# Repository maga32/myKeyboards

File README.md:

[<< 키보드 종류 보기](../../)

---

# GripKey

<br>

조이콘처럼 한손/양손에 쥐고 사용하는 마우스 겸 키보드 

## 1. 특징

### 1.1. 한손에 쥐고 사용가능한 가벼움과 편리성

- 한손에 쥐고 사용 가능한 크기와 무게로 제작되어 손목에 부담이 없습니다.
- 각각 1000mAh 배터리를 탑재하여 장시간 사용 가능합니다.
- 따로 키보드 위치를 고정해놓을 필요가 없어, 편한 자세로 누워서 사용하기에도 좋습니다.
- !! 한쪽 기기만 사용하여 휴대폰, 태블릿으로 웹툰/소설/쇼츠 감상용으로 사용하기에도 매우 유용합니다. !!
<br>
<br>

### 1.2. 부족함없는 키 개수와 기능
<br>

- 한쪽당 (5x3 +3) 18키로, 양쪽 모두 사용시 36키가 되어 일반적인 키보드의 기능을 모두 활용할 수 있습니다.
- 추가로 5방향(상,하,좌,우,클릭) 조이스틱이 탑재되어 마우스, 방향키, 스크롤등이 편하게 사용가능합니다.
- 각각 휠이 달려있어 스크롤, 음량, 밝기 조절, 확대축소 등을 빠르게 졉근할 수 있습니다.
<br>

### 1.3. zmk 기반
- zmk기반으로 usb연결, 블루투스 4기기 멀티페어링 등이 가능합니다.
- 동글모드, 키맵핑 수정, 매크로 등 zmk에서 지원하는 모든 기능이 커스텀 가능합니다.
- 한손만으로 사용 가능하도록 오른손을 마스터로 사용하였습니다. (zmk 수정으로 왼손 변경가능)

<br>
<br>

## 2. 제작기
[바로가기](./note/)

## 3. 필요 재료
| 이름                | 설명               | 한쪽당 수량 | 양쪽 수량 | 구매처 |
|--------------------|-------------------------|------|-------|--------|
| mcu(nrf52840)      | Nice!Nano2.0 호환 기판    | 1  | 2  | AliExpress |
| 스위치 & 리셋스위치   | 6x6x7.3mm                | 19 | 38 | 네이버스토어 |
| Row 연결용 다이오드   | 1N4148                  | 18 | 36 | AliExpress |
| 슬라이드 전원 스위치   | SS12D00 4mm             | 1  | 2  | AliExpress |
| 리튬폴리머 배터리     | TW102050 1000mAh         | 1  | 2  | 디바이스마트 |
| M2 십자 볼트         | M2 5mm                  | 6  | 12 | 네이버스토어 |
| M2 인서트 너트       | M2 3mm (외경 2.81mm)     | 6  | 12 | AliExpress |
| 5방향 스위치(조이스틱) | 7x7x6mm (대각선방향 스틱)  | 1  | 2  | AliExpress |
| 휠- 로터리 인코더     | Kailh 5mm 마우스 인코더   | 1  | 2  | AliExpress |
| 휠- MR63 베어링     | MR63 3x6x2mm            | 1  | 2  | AliExpress |
| 휠- M3 기둥         | M3 6mm 원형 샤프트        | 1  | 2  | AliExpress |
| 마그네틱 커넥터       | (대체가능)셀인스텍 PD-I100W | 1  | 2  | 네이버스토어 |
| AWG30 케이블        | 전선 연결용                | 0  | 1  | 디바이스마트 |

!! 상단의 재료 기준은 최소 수량입니다. 여유있게 구매하는걸 추천드립니다. !!

## 4. 모델링 파일
3d 프린터로 출력할 수 있는 .stl 파일입니다.<br>
[바로가기](./stl/)

## 5. 펌웨어(zmk)
ble(저전력 블루투스)를 지원하는 zmk를 이용하여 만들었습니다.<br>
[바로가기](https://github.com/maga32/GripKey-config)

## 6. 갤러리
[바로가기](./images_orig)

---

[<< 키보드 종류 보기](../../)

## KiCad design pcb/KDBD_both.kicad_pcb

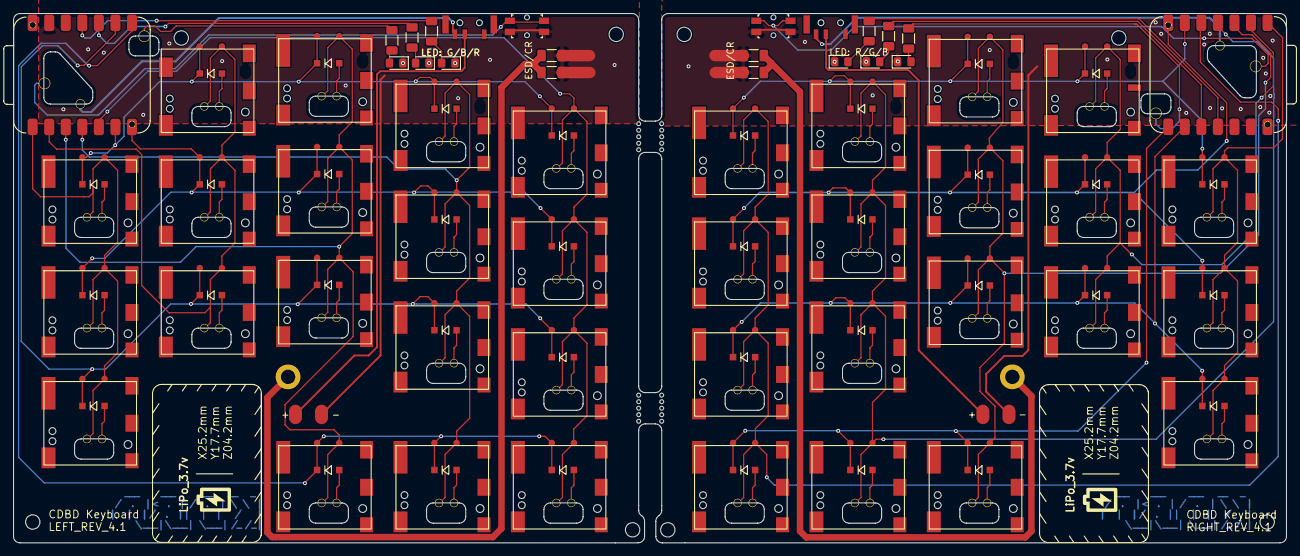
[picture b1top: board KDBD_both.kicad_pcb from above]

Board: 2 copper layers, 195.3 x 81.2 mm, 68 parts (0 on the bottom side), 72 nets.

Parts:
C1, C1#2: C_1206_3216Metric_Pad1.33x1.80mm_HandSolder
H1, H2: mounting_hole_plated
L1, L1#2, L2, L2#2, L3, L3#2: LED_0805_2012Metric_Pad1.15x1.40mm_HandSolder
MCU1, MCU2: XIAO-nRF52840-SMD; XIAO-nRF52840
MH1, MH2, MH3, MH4, MH5, MH6, MH7, MH8: mounting_hole_npth
R1, R1#3, R2, R2#2, R3, R3#2: R_1206_3216Metric_Pad1.30x1.75mm_HandSolder
R1#2, R1#4: C_1206_3216Metric_Pad1.33x1.80mm_HandSolder
RST1, RST2: reset_switch_smd_side
SW1, SW2, SW3, SW4, SW5, SW6, SW7, SW8, SW9, SW10, SW11, SW12, SW13, SW14, SW15, SW16, SW17, SW18, SW19, SW20, SW21, SW22, SW23, SW24, SW25, SW26, SW27, SW28, SW29, SW30, SW31, SW32, SW33, SW33#2, SW34, SW152: ULP_SW; GENERIC_ULP_HANDSOLDER
TH1, TH2: simple_tht_fp

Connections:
L_C1: MCU2.1, SW1.1, SW2.1, SW3.1
L_C2: MCU2.2, SW4.1, SW5.1, SW6.1
L_C3: MCU2.3, SW7.1, SW8.1, SW9.1, SW152.1
L_C4: MCU2.4, SW10.1, SW11.1, SW12.1, SW16.1
L_C5: MCU2.5, SW13.1, SW14.1, SW15.1, SW17.1
L_CGND: C1#2.1, R1#2.1
L_GND: C1#2.2, L1.1, L2#2.1, L3#2.1, MCU2.13, R1#2.2, RST1.2, RST1.4, TH1.1
L_LED1: L1.2, R1#3.2
L_LED2: L2#2.2, R2#2.2
L_LED3: L3#2.2, R3#2.2
L_LED_R1: MCU2.11, R1#3.1
L_LED_R2: MCU2.10, R2#2.1
L_LED_R3: MCU2.17, R3#2.1
L_R1: MCU2.6, SW3.4, SW6.4, SW9.4, SW12.4, SW15.4
L_R2: MCU2.7, SW2.4, SW5.4, SW8.4, SW11.4, SW14.4
L_R3: MCU2.9, SW1.4, SW4.4, SW7.4, SW10.4, SW13.4
L_R4: MCU2.8, SW16.4, SW17.4, SW152.4
L_RST: MCU2.21, RST1.1, RST1.3
R_C1: MCU1.1, SW18.1, SW19.1, SW20.1
R_C2: MCU1.2, SW21.1, SW22.1, SW23.1
R_C3: MCU1.3, SW24.1, SW25.1, SW26.1, SW33.1
R_C4: MCU1.4, SW27.1, SW28.1, SW29.1, SW33#2.1
R_C5: MCU1.5, SW30.1, SW31.1, SW32.1, SW34.1
R_CGND: C1.2, R1#4.2
R_GND: C1.1, L1#2.1, L2.1, L3.1, MCU1.13, R1#4.1, RST2.2, RST2.4, TH2.1
R_LED1: L1#2.2, R1.1
R_LED2: L2.2, R2.1
R_LED3: L3.2, R3.1
R_LED_R1: MCU1.11, R1.2
R_LED_R2: MCU1.10, R2.2
R_LED_R3: MCU1.17, R3.2
R_R1: MCU1.6, SW20.4, SW23.4, SW26.4, SW29.4, SW32.4
R_R2: MCU1.7, SW19.4, SW22.4, SW25.4, SW28.4, SW31.4
R_R3: MCU1.9, SW18.4, SW21.4, SW24.4, SW27.4, SW30.4
R_R4: MCU1.8, SW33.4, SW33#2.4, SW34.4
R_RST: MCU1.21, RST2.1, RST2.3
SW1_1: SW1.2, SW1.5
SW2_1: SW2.2, SW2.5
SW3_1: SW3.2, SW3.5
SW4_1: SW4.2, SW4.5
SW5_1: SW5.2, SW5.5
SW6_1: SW6.2, SW6.5
SW7_1: SW7.2, SW7.5
SW8_1: SW8.2, SW8.5
SW9_1: SW9.2, SW9.5
SW10_1: SW10.2, SW10.5
SW11_1: SW11.2, SW11.5
SW12_1: SW12.2, SW12.5
SW13_1: SW13.2, SW13.5
SW14_1: SW14.2, SW14.5
SW15_1: SW15.2, SW15.5
SW15_2: SW152.2, SW152.5
SW16_1: SW16.2, SW16.5
SW17_1: SW17.2, SW17.5
SW18_1: SW18.2, SW18.5
SW19_1: SW19.2, SW19.5
SW20_1: SW20.2, SW20.5
SW21_1: SW21.2, SW21.5
SW22_1: SW22.2, SW22.5
SW23_1: SW23.2, SW23.5
SW24_1: SW24.2, SW24.5
SW25_1: SW25.2, SW25.5
SW26_1: SW26.2, SW26.5
SW27_1: SW27.2, SW27.5
SW28_1: SW28.2, SW28.5
SW29_1: SW29.2, SW29.5
SW30_1: SW30.2, SW30.5
SW31_1: SW31.2, SW31.5
SW32_1: SW32.2, SW32.5
SW33_1: SW33#2.2, SW33#2.5
SW33_2: SW33.2, SW33.5
SW34_1: SW34.2, SW34.5

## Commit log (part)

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2024-10-20 내용작성
2024-11-14 README.md 현재 레포에 맞게 수정
2024-11-14 peachKB-MK-II 추가
2024-11-14 corne35 추가
2024-11-15 peachKB, peachKB-MK-II, corne35 레포지토리 통합
2026-05-06 pcb추가
